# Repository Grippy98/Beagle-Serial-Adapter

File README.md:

# Beagle-Serial-Adapter
A CH340E Based Minimalist USB-Serial Adapter for BeaglePlay, AI64 and More.

The board is 4 layers and features components mainly sourced from LCSC for cost effectiveness and ease of building via JLC PCB or similar. 
It is designed in KiCAD 7.0.9.

Front           |  Back
:-------------------------:|:-------------------------:
  |  

> [!NOTE]  
> The header at the bottom should be Female to mate with BeaglePlay, not male as shown in the 3D render.

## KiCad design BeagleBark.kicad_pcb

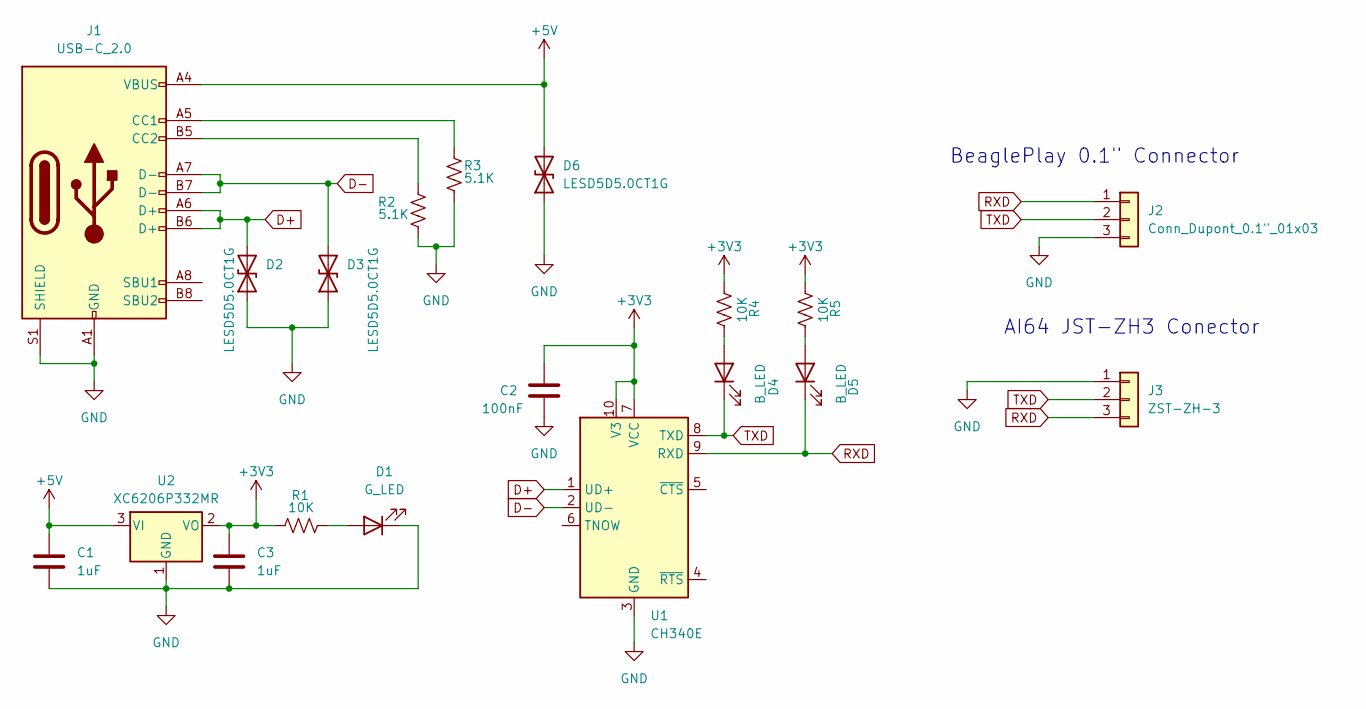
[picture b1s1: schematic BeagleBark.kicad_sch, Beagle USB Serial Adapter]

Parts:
C1, C3: 1uF; C_0402_1005Metric
C2: 100nF; C_0402_1005Metric
D1: G_LED; LED_0402_1005Metric
D2, D3, D6: LESD5D5.0CT1G; D_SOD-523
D4, D5: B_LED; LED_0402_1005Metric
J1: USB-C_2.0; TYPE-C-31-M-12
J2: Conn_Dupont_0.1"_01x03; PinHeader_1x03_P2.54mm_Horizontal
J3: ZST-ZH-3; JST_ZH_B3B-ZR_1x03_P1.50mm_Vertical
R1, R4, R5: 10K; R_0402_1005Metric
R2, R3: 5.1K; R_0402_1005Metric
U1: CH340E; MSOP-10_3x3mm_P0.5mm
U2: XC6206P332MR; SOT-23-3

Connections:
+3V3: C2.1, C3.1, R1.1, R4.1, R5.1, U1.7 (VCC), U1.10 (V3), U2.2 (VO)
+5V: C1.1, D6.2 (A2), J1.A4 (VBUS), J1.A9 (VBUS), J1.B4 (VBUS), J1.B9 (VBUS), U2.3 (VI)
D+: D2.2 (A2), J1.A6 (D+), J1.B6 (D+), U1.1 (UD+)
D-: D3.2 (A2), J1.A7 (D-), J1.B7 (D-), U1.2 (UD-)
GND: C1.2, C2.2, C3.2, D1.1 (K), D2.1 (A1), D3.1 (A1), D6.1 (A1), J1.A1 (GND), J1.A12 (GND), J1.B1 (GND), J1.B12 (GND), J1.S1 (SHIELD), J2.3, J3.1, R2.2, R3.2, U1.3 (GND), U2.1 (GND)
unnamed: D1.2 (A), R1.2
unnamed: D4.2 (A), R4.2
unnamed: D5.2 (A), R5.2
unnamed: J1.A5 (CC1), R3.1
unnamed: J1.B5 (CC2), R2.1
RXD: D5.1 (K), J2.1, J3.3, U1.9 (RXD)
TXD: D4.1 (K), J2.2, J3.2, U1.8 (TXD)

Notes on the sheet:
AI64 JST-ZH3 Conector
BeaglePlay 0.1" Connector

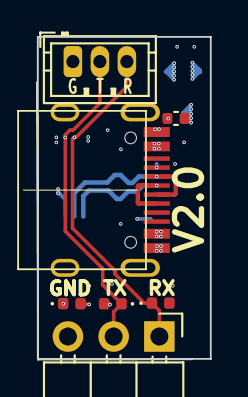
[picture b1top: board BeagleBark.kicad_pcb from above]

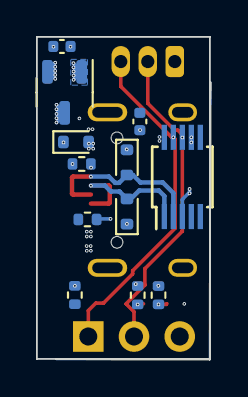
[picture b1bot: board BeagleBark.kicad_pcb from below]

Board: 4 copper layers, 9.6 x 17.9 mm, 19 parts (12 on the bottom side), 12 nets.

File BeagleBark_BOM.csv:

"Id";"Designator";"Footprint";"Quantity";"Designation";"Supplier and ref";
1;"J3";"JST_ZH_B3B-ZR_1x03_P1.50mm_Vertical";1;"ZST-ZH-3";;;
2;"D1";"LED_0402_1005Metric";1;"G_LED";;;
3;"J2";"PinHeader_1x03_P2.54mm_Horizontal";1;"Conn_Dupont_0.1"_01x03";;;
4;"J1";"TYPE-C-31-M-12";1;"USB-C_2.0";;;
5;"D5,D4";"LED_0402_1005Metric";2;"B_LED";;;
6;"C1,C3";"C_0402_1005Metric";2;"1uF";;;
7;"U2";"SOT-23-3";1;"XC6206P332MR";;;
8;"R2,R3";"R_0402_1005Metric";2;"5.1K";;;
9;"R5,R4,R1";"R_0402_1005Metric";3;"10K";;;
10;"D3,D2,D6";"D_SOD-523";3;"LESD5D5.0CT1G";;;
11;"U1";"MSOP-10_3x3mm_P0.5mm";1;"CH340E";;;
12;"C2";"C_0402_1005Metric";1;"100nF";;;

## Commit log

2023-12-21 Table Update
2023-12-22 Added Gerbers
2023-12-22 Added note
